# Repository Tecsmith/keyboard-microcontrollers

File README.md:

# Keyboard Microcontrollers

A collection of KiCAD Microcontroller templates covering various common MCUs used in developing custom keyboards.

This repo is set up for learning and you are welcome to copy and paste the components into your own project. License is [MIT](/LICENSE.md) giving you the freadom to use it as you wish.

## Embedded MCUs

> :information_source: This section WIP.

### STMicroelectronics (STM32)

<!-- This may work better as a table with core specs -->

| Folder | Vendor Link |
| -- | -- |
| STM32G0B1 | [STM32G0B1](https://www.st.com/en/microcontrollers-microprocessors/stm32g0x1.html) :arrow_heading_up: <blockquote>TBD</blockquote> |
| [STM32G474](./stm32g474/) | [STM32G474](https://www.st.com/en/microcontrollers-microprocessors/stm32g4x4.html) :arrow_heading_up: |

 <!-- * [STM32F0x2](https://www.st.com/en/microcontrollers-microprocessors/stm32f0x2.html) -->
 <!-- * [STM32F103](https://www.st.com/en/microcontrollers-microprocessors/stm32f103.html)
   * Bluepill (with STM32duino bootloader) -->
 <!-- * [STM32F303](https://www.st.com/en/microcontrollers-microprocessors/stm32f303.html)
   * QMK Proton-C -->
 <!-- * [STM32F401](https://www.st.com/en/microcontrollers-microprocessors/stm32f401.html)
   * WeAct Blackpill -->
 <!-- * [STM32F405](https://www.st.com/en/microcontrollers-microprocessors/stm32f405-415.html) -->
 <!-- * [STM32F407](https://www.st.com/en/microcontrollers-microprocessors/stm32f407-417.html) -->
 <!-- * [STM32F411](https://www.st.com/en/microcontrollers-microprocessors/stm32f411.html)
   * WeAct Blackpill -->
 <!-- * [STM32F446](https://www.st.com/en/microcontrollers-microprocessors/stm32f446.html) -->
 <!-- * [STM32G431](https://www.st.com/en/microcontrollers-microprocessors/stm32g4x1.html) -->
 <!-- * [STM32H723](https://www.st.com/en/microcontrollers-microprocessors/stm32h723-733.html) -->
 <!-- * [STM32H733](https://www.st.com/en/microcontrollers-microprocessors/stm32h723-733.html) -->
 <!-- * [STM32L412](https://www.st.com/en/microcontrollers-microprocessors/stm32l4x2.html) -->
 <!-- * [STM32L422](https://www.st.com/en/microcontrollers-microprocessors/stm32l4x2.html) -->
 <!-- * [STM32L432](https://www.st.com/en/microcontrollers-microprocessors/stm32l4x2.html) -->
 <!-- * [STM32L433](https://www.st.com/en/microcontrollers-microprocessors/stm32l4x3.html) -->
 <!-- * [STM32L442](https://www.st.com/en/microcontrollers-microprocessors/stm32l4x2.html) -->
 <!-- * [STM32L443](https://www.st.com/en/microcontrollers-microprocessors/stm32l4x3.html) -->

### Raspberry Pi

| Folder | Vendor Link |
| --- | --- |
| RP2040 | [RP2040](https://www.raspberrypi.com/documentation/microcontrollers/rp2040.html) <blockquote>TBD</blockquote> |

## Embeddable MCU Modules

> :information_source: This section TBD.

| Folder | MCU | Vendor Link |
| --- | --- | --- |
| EByte E73 | nRF52840 | [E73](https://www.cdebyte.com/products/E73-2G4M08S1C) <blockquote>TBD</blockquote> |

<!--
## *(Stand-alone)* MCU Modules

> :information_source: This section TBD.

| Folder | MCU | Vendor Link |
| --- | --- | --- |
| Xiao RP2040 | RP2040 | [Xiao RP2040](https://wiki.seeedstudio.com/XIAO-RP2040/) <blockquote>TBD</blockquote> |
| XIAO nRF52840 | nRF52840 | [XIAO BLE](https://wiki.seeedstudio.com/XIAO_BLE/) <blockquote>TBD</blockquote> |
-->

---

Made with :heart:

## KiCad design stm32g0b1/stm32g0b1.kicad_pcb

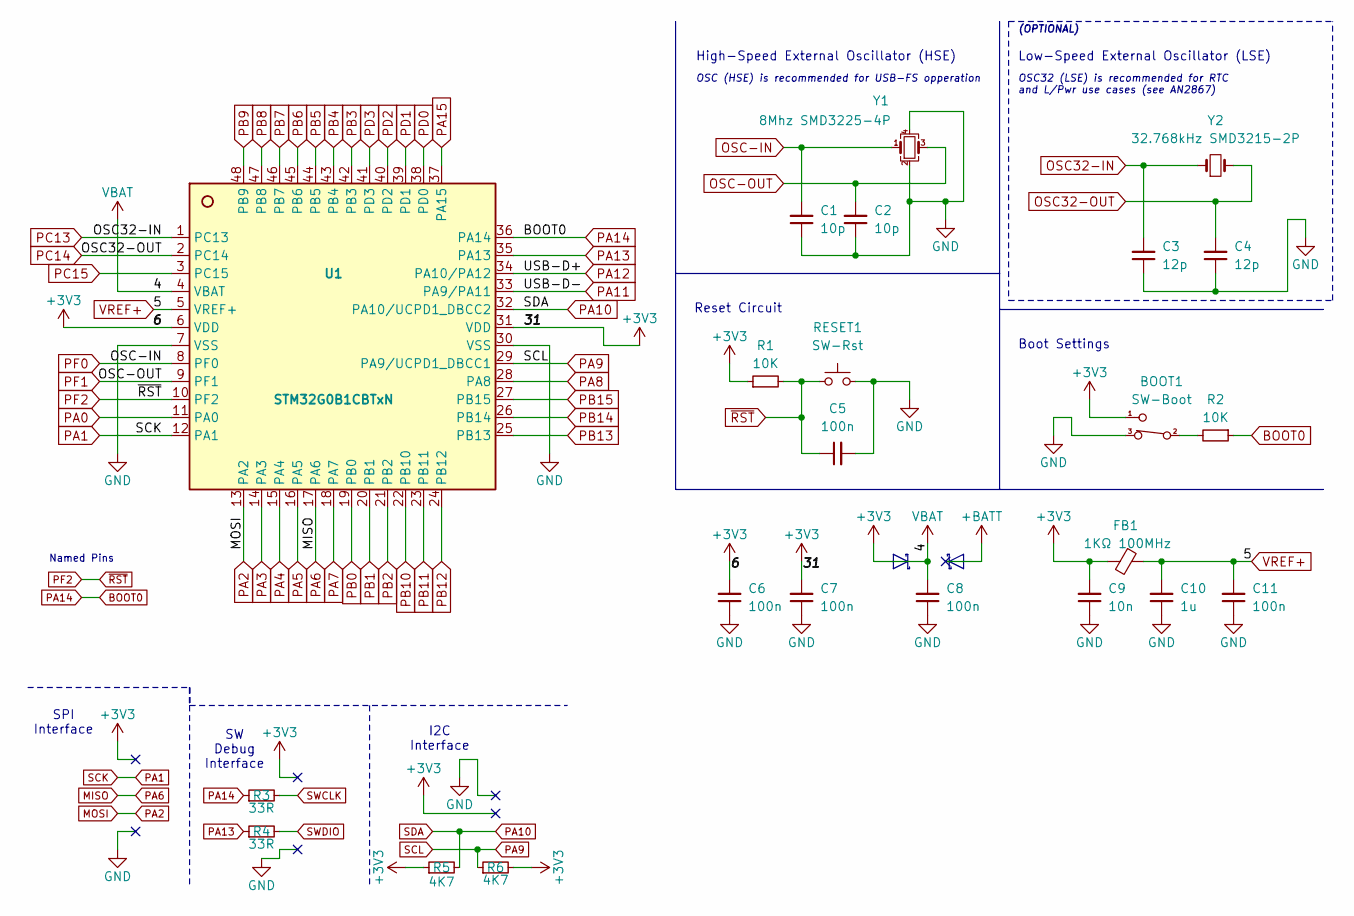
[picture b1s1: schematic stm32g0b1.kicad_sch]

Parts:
BOOT1: SW-Boot; SW_SPDT_PCM12
C1, C2: 10p; C_0603_1608Metric
C3, C4: 12p; C_0603_1608Metric
C5, C6, C7, C8, C11: 100n; C_0603_1608Metric
C9: 10n; C_0603_1608Metric
C10: 1u; C_0603_1608Metric
FB1: 1KΩ 100MHz; L_0603_1608Metric; LCSC C13572
R1, R2: 10K; R_0603_1608Metric
R3, R4: 33R; R_0603_1608Metric
R5, R6: 4K7; R_0603_1608Metric
RESET1: SW-Rst; SW_SPST_TS-1088-xR020
U1: STM32G0B1CBTxN; LQFP-48_7x7mm_P0.5mm
Y1: 8Mhz SMD3225-4P; Crystal_SMD_3225-4Pin_3.2x2.5mm; LCSC C2682775
Y2: 32.768kHz SMD3215-2P; Crystal_SMD_3215-2Pin_3.2x1.5mm; LCSC C156245

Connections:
+3V3: BOOT1.1 (A), C6.2, C7.2, C8.2, C9.2, FB1.2, R1.1, R5.1, R6.2, U1.4 (VBAT), U1.6 (VDD), U1.31 (VDD)
BOOT0: R2.1, R3.1, U1.36 (PA14)
GND: BOOT1.3 (C), C1.1, C2.1, C3.1, C4.1, C5.2, C6.1, C7.1, C8.1, C9.1, C10.1, C11.1, RESET1.2, U1.7 (VSS), U1.30 (VSS), Y1.2, Y1.4
MISO: U1.17 (PA6)
MOSI: U1.13 (PA2)
unnamed: BOOT1.2 (B), R2.2
OSC32-IN: C3.2, U1.1 (PC13), Y2.1
OSC32-OUT: C4.2, U1.2 (PC14), Y2.2
OSC-IN: C1.2, U1.8 (PF0), Y1.1
OSC-OUT: C2.2, U1.9 (PF1), Y1.3
PA0: U1.11 (PA0)
PA1: U1.12 (PA1)
PA3: U1.14 (PA3)
PA4: U1.15 (PA4)
PA5: U1.16 (PA5)
PA7: U1.18 (PA7)
PA8: U1.28 (PA8)
PA9: R6.1, U1.29 (PA9/UCPD1_DBCC1)
PA10: R5.2, U1.32 (PA10/UCPD1_DBCC2)
PA11: U1.33 (PA9/PA11)
PA12: U1.34 (PA10/PA12)
PA13: R4.1, U1.35 (PA13)
PA15: U1.37 (PA15)
PB0: U1.19 (PB0)
PB1: U1.20 (PB1)
PB2: U1.21 (PB2)
PB3: U1.42 (PB3)
PB4: U1.43 (PB4)
PB5: U1.44 (PB5)
PB6: U1.45 (PB6)
PB7: U1.46 (PB7)
PB8: U1.47 (PB8)
PB9: U1.48 (PB9)
PB10: U1.22 (PB10)
PB11: U1.23 (PB11)
PB12: U1.24 (PB12)
PB13: U1.25 (PB13)
PB14: U1.26 (PB14)
PB15: U1.27 (PB15)
PC15: U1.3 (PC15)
PD0: U1.38 (PD0)
PD1: U1.39 (PD1)
PD2: U1.40 (PD2)
PD3: U1.41 (PD3)
PF2: C5.1, R1.2, RESET1.1, U1.10 (PF2)
SWCLK: R3.2
SWDIO: R4.2
VREF+: C10.2, C11.2, FB1.1, U1.5 (VREF+)

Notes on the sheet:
(OPTIONAL)
Low-Speed External Oscillator (LSE)
Boot Settings
Reset Circuit
OSC (HSE) is recommended for USB-FS opperation
OSC32 (LSE) is recommended for RTC and L/Pwr use cases (see AN2867)
High-Speed External Oscillator (HSE)
I2C Interface
SPI Interface
Named Pins
SW Debug Interface

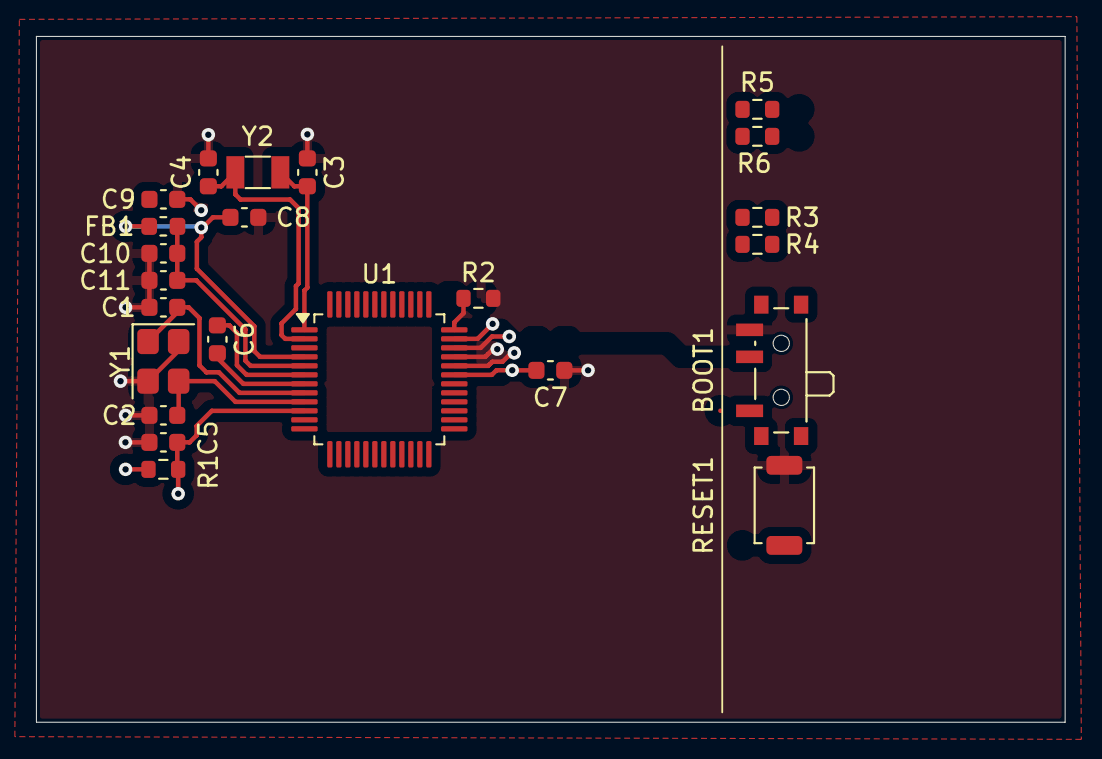
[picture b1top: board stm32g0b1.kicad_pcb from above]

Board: 2 copper layers, 57.1 x 38.1 mm, 23 parts (0 on the bottom side), 13 nets.

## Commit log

2025-11-18 Added STM32G474
2025-11-20 update-2025-11-20
2025-11-20 Added STM32G0B1
